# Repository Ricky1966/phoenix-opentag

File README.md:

# Phoenix OpenTag

> [!CAUTION]
> **Experimental hobby project: use it entirely at your own risk.** It comes with no warranty, and the author is **not responsible** for any damage to printers, PCs, hardware, software or data. Read the Disclaimer section of this README before you build, flash or run anything.
>
> *Progetto sperimentale: uso a proprio rischio e pericolo. L'autore non risponde di alcun danno a stampanti, computer, hardware, software o dati.*

A minimal NFC reader and writer for **OpenPrintTag** tags (the Prusa Research standard), based on an **ESP32 + PN5180** and designed to be connected to the Sovol SV08 "Phoenix".

Born as a reduced version of [Odin-ESP32](https://github.com/Ricky1966/Odin-ESP32) (a filament drying station): the hardware initialization comes from Odin's `develop` branch, with a separate parser and checks on NFC reads, but without the web dashboard, heater, environment sensors or multi-spool handling. It validates the reads and integrates with Spoolman and Moonraker.

## ⚠️ Disclaimer: use at your own risk

Phoenix OpenTag is an experimental hobby project, provided **"as is"**, without warranty of any kind. It means flashing firmware, wiring electronics, writing to NFC tags, sending commands to a printer's firmware (Klipper/Moonraker) and installing software on your computers. Mistakes, bugs or incompatibilities can cause failed prints, damage to your printer(s), your computer(s), the ESP32/PN5180 module, the tags or any other hardware or software, loss of data, or other harm.

By building, installing, running or modifying anything here you accept that you do so **entirely at your own risk**. The author and the contributors are **not responsible or liable** for any damage or loss of any kind: printers, PCs, hardware, software, data or anything else. Test carefully, never leave a printer unattended, back up your configuration before changing it, and read the code before you run it. The warranty disclaimer of the AGPL-3.0 licence (sections 15 and 16) applies as well.

*In italiano: progetto sperimentale da usare **a proprio rischio e pericolo**. L'autore non risponde di alcun danno a stampanti, computer, hardware, software o dati.*

---

## What it does

- Connects to the home WiFi (station mode, no Access Point), used for sending in `wifi`/`auto` mode and for OTA updates.
- Continuously reads the ISO15693/NFC-V tags near the PN5180 (the protocol used by OpenPrintTag).
- When it recognizes an OpenPrintTag, it prints on the serial port: brand, material, colour, diameter, density, nozzle/bed temperature range, weight, country.
- Prints the data when the tag changes or a valid read is recovered. It only sends validated data.
- Sends every new read to the daemon on Phoenix, over **USB** or **WiFi** as you choose (see below). The daemon passes it to Spoolman and sets the active spool in Moonraker.
- **Writes** OpenPrintTag images to blank or existing ICODE SLIX2 tags, driven by the Spoolman fork's «Scrivi tag» button, and offers to write a blank tag when one is placed on the reader (see below).

## Writing tags

The firmware writes complete OpenPrintTag images to **ICODE SLIX2 tags with 316 user bytes**, with UID check, protection checks, explicit consent to replace existing data and a full read-back. Serial protocol, command-line client and limits: [procedure and limits](docs/tag-writing.md).

With the [Spoolman fork](https://github.com/Ricky1966/Spoolman) the whole flow runs from the web UI: open a saved spool, press **Scrivi tag**, check the pre-filled data, place the tag and confirm. The tag is linked to the spool only after the firmware has verified it. Validated on real hardware on 1 October 2026. Setup of the authenticated bridge between Spoolman and the daemon is described in [docs/tag-writing.md](docs/tag-writing.md).

A **blank** SLIX2 tag placed on the reader while the printer is idle is reported to Spoolman, which proposes the spool without a tag and asks for confirmation before writing; after a verified write the tag is read again and the spool becomes active. The reader stays disarmed while a print is running or paused, or while Klipper is running G-code (macros, filament loading).

## Hardware

- ESP32 DevKit, 38 pin (AZ-Delivery ESP32-WROOM-32)
- PN5180 module (NXP/AZ-Delivery breakout)
- ICODE SLIX2 tags, jumper wires and a USB data cable

The full **bill of materials**, tag requirements and the **wiring schematic** are in [docs/hardware.md](docs/hardware.md).

Point-to-point wiring:

| PN5180 signal | ESP32 GPIO |
|---|---|
| RST | 17 |
| NSS (CS) | 5 |
| MOSI | 23 |
| MISO | 19 |
| SCK / CLK | 18 |
| BUSY | 16 |
| 5V | 5V |
| 3V3 | 3V3 |
| GND | GND |

## Setup

```bash
cp src/secrets.h.example src/secrets.h
# edit src/secrets.h with the real WiFi SSID/password
pio run --target upload
pio device monitor
```

`src/secrets.h` is not versioned (see `.gitignore`).

## Updating over WiFi (OTA)

Since 0.4.0 the firmware can also be updated over WiFi, without unplugging the ESP32 from Phoenix. WiFi always stays on, even in `usb` mode, because OTA needs it.

1. In `src/secrets.h` add the OTA password (see `secrets.h.example`); without this line OTA stays disabled:
   ```c
   #define OTA_PASSWORD "choose-a-password"
   ```
2. **Once, over USB**, flash the first firmware that has OTA: `pio run -t upload --upload-port <port>`. At start-up you must see `OTA attivo: phoenix-opentag.local (<IP>)`.
3. From then on, from the PC:
   ```bash
   PHOENIX_OTA_PASSWORD='choose-a-password' pio run -e esp32dev_ota -t upload
   ```
   If `phoenix-opentag.local` does not resolve, add `--upload-port <ESP32 IP>` (printed by `show`).

Use only letters and digits for `OTA_PASSWORD`: PlatformIO inserts it into the command without quotes, so `&`, `;`, `$` or spaces break it. `espota.py --debug` prints the password in clear text: do not use it. The password is compiled into the firmware, so changing it requires a new flash over USB.

During the update NFC reading is paused; when it finishes the ESP32 restarts and the daemon on Phoenix resumes reading the serial port by itself.

## Sending to Phoenix: USB or WiFi

The mode is chosen from the serial port (`pio device monitor`, 115200) and is kept in flash, with no recompilation:

| Command | Effect |
|---|---|
| `show` | current settings |
| `mode usb` | every read goes out on the serial port as a `PHOENIX-TAG {json}` line, read by the daemon (default) |
| `mode wifi` | HTTP `POST <host>/tag` with the same JSON |
| `mode auto` | WiFi if connected and the POST succeeds, otherwise USB |
| `host http://<phoenix-ip>:7913` | address of the daemon on Phoenix |
| `reader <id>` | `reader_id` shown in Spoolman (default `phoenix-opentag`) |
| `test` | resend the last tag read |
| `reboot` | restart, required after `mode` |

The initial values are in `src/config.h` (`TRANSPORT_DEFAULT_*`). JSON v1 sent since version 0.5 (fields missing from the tag are omitted; the daemon also accepts the 0.4 names):

```json
{"schema_version":1,"event_id":"12ab34cd-00000001","uid":"E004010812345678","reader_id":"phoenix-opentag","firmware":"0.5.0-dev","brand_name":"Prusament","material_name":"PLA Galaxy Black","color_rgba":"#3D3E3DFF","filament_diameter":1.75,"density":1.24,"nominal_netto_full_weight":1000}
```

The firmware keeps only the latest valid read: it retries after 5, 10, 20, 40 and 60 seconds (maximum), pauses sending on an NFC error and cancels the event when the removal is confirmed. Over USB the daemon replies `ack <event_id>` only after successful handling; over WiFi a Moonraker error produces HTTP 502. The two transports share the same event in `auto` mode. POSTs are synchronous and can temporarily delay NFC polling and OTA. The full contract is in [docs/http-contract.md](docs/http-contract.md).

An activation refused during `printing`/`paused` is a final outcome: it is not queued for the end of the print. After the print you need a new read, or `test`. The weights of spools that are already registered are not updated from the tag.

**Upgrading from 0.4:** install the new daemon first (it is compatible with both formats), then the firmware. Restart only `phoenix-opentag` after updating the files. Verify with a known spool, with the printer idle. Keep `src/secrets.h`, the NVS settings and the `--serial` parameters of the existing service.

## Daemon on Phoenix

`host/phoenix_opentag_daemon.py` runs on the CB1 with the system `python3` (no dependencies). For every read:

1. it calls `POST /api/v1/tag/scan` on Spoolman (≥ 0.27.0), which resolves the UID to the linked spool;
2. if the UID is unknown and the tag carries at least `material` and `density`, it creates the spool, reusing the vendor (`brand`) and filament (name, vendor, colour, diameter) if they already exist, and links the tag to it;
3. it sets the active spool with `POST /server/spoolman/spool_id` on Moonraker, **but not if the printer is `printing` or `paused`**.
4. with `--lane-data` (off by default), it also publishes the active spool to Moonraker's `lane_data` database namespace, see [Loading the filament profile in OrcaSlicer](#loading-the-filament-profile-in-orcaslicer-optional).

Only consecutive identical events handled successfully within 5 s are deduplicated; A → B → A reactivates A. Temporary errors are not remembered as successes. Useful options: `--no-create`, `--no-activate`, `--lane-data`, `-v`.

### Loading the filament profile in OrcaSlicer (optional)

> **Experimental, not yet tested with OrcaSlicer.** Unreleased: the `filament_id` part needs a small OrcaSlicer patch (`orca-patches/0003-moonraker-lane-data-filament-id.patch` in the `sv08-ultimate-build-dev` repository, not merged upstream). Without it, Orca still reads the material, colour and temperatures but picks a generic profile.

With `--lane-data`, after the spool is activated the daemon writes one lane to Moonraker's database (`POST /server/database/item`, namespace `lane_data`, key `lane<N>`, with `N` from `--lane-index`, default `0`):

```json
{"lane": "0", "material": "PLA", "color": "#A1B2C3", "nozzle_temp": 215, "bed_temp": 60, "filament_id": "OFW29a9R"}
```

It is built from the Spoolman filament: `material`, `color_hex`, `settings_extruder_temp`, `settings_bed_temp`, and an optional **text** extra field `orca_filament_id` (create it in Spoolman under Settings → Extra fields → Filament) holding the `filament_id` of the OrcaSlicer profile. The lane is skipped if the filament has no material. A failure here is logged and never undoes the activation. Nothing is written while the printer is `printing` or `paused`, because the activation is skipped then.

The lane also carries two informational fields that OrcaSlicer ignores: `name` (vendor and filament name) and `updated` (UNIX seconds of the read), so a tool can show which tag the lane comes from.

In OrcaSlicer, press *Synchronize filament list* in the sidebar to load the profile: nothing changes by itself. To read what Orca will see: `curl -s "http://localhost:7125/server/database/item?namespace=lane_data"`.

```bash
# manual test on Phoenix
python3 ~/phoenix-opentag/host/phoenix_opentag_daemon.py --listen 0.0.0.0:7913 \
    --serial /dev/serial/by-id/usb-1a86_USB_Serial-if00-port0   # only for usb/auto
curl -s http://localhost:7913/health

# permanent service
sudo cp ~/phoenix-opentag/host/phoenix-opentag.service /etc/systemd/system/
sudo systemctl daemon-reload && sudo systemctl enable --now phoenix-opentag
journalctl -u phoenix-opentag -f
```

To switch the service to USB mode, add `--serial` to the `--listen` line and restart it:

```bash
sudo sed -i 's|--listen 0.0.0.0:7913 \\|--listen 0.0.0.0:7913 --serial /dev/serial/by-id/usb-1a86_USB_Serial-if00-port0 \\|' /etc/systemd/system/phoenix-opentag.service
sudo systemctl daemon-reload && sudo systemctl restart phoenix-opentag
```

To send commands to the ESP32 while it is connected to Phoenix, stop the daemon (`sudo systemctl stop phoenix-opentag`: the port must not be read by two programs) and use the serial monitor included with Klipper. Exit with `Ctrl+]`, which on an Italian keyboard is `Ctrl+5`:

```bash
~/klippy-env/bin/python -m serial.tools.miniterm -e /dev/serial/by-id/usb-1a86_USB_Serial-if00-port0 115200
```

With `--serial` always use the `/dev/serial/by-id/...` path of the ESP32. The daemon refuses to open a port that appears as `serial:` in Klipper's `.cfg` files (`--klipper-config`, default `~/printer_data/config`).

The daemon and Spoolman have no authentication: expose them only on the local network. The writer API of the daemon is disabled unless `PHOENIX_WRITER_TOKEN` is set.

## Validation

PC tests: parser, delivery, ISO15693 driver, 40,000 altered inputs, the six official OpenPrintTag tags, the writer (interruptions at every block, locks, an unwritable block 79) and daemon/bridge regressions (see "PC tests").

**1 October 2026, tag writing: PASS on real hardware.** Writing failed at first because ICODE SLIX2 block 79 is a read-only counter, not user memory; after limiting the writer to the 316 user bytes (blocks 0–78) a tag was restored from a backup (`verified: true`, block 79 untouched), then written from the Spoolman web UI: verified by the firmware, linked to the spool, re-read without creating a duplicate, and the spool made active in Moonraker.

**30 September 2026, consolidated version `0.5.0-dev`: PASS on real hardware.** Flash over USB, then a successful **OTA update over WiFi** with the final password. At start-up: WiFi connected, PN5180 3.5 OK, `OTA attivo`. The ODIN test tag is read and sent as a `PHOENIX-TAG` line (JSON v1). The daemon of this branch, installed on Phoenix in place of the previous version, finds spool 2 again in USB mode (`created: false`) and activates it in Moonraker. Locally, with Spoolman 0.27.0, the daemon creates vendor, filament, spool and link from the firmware line, replies `ack <event_id>`, ignores a repeated `event_id` and does not activate the spool while the printer is `printing`.

Still to verify: that the ESP32 really receives the ACK from the daemon, the `wifi` and `auto` modes with the consolidated firmware, the blank-tag proposal on a real blank tag, and the reading of tags not written by Odin.

Earlier tests, on version 0.4 (0.4 daemon):

**29 September 2026, WiFi mode: PASS on real hardware.** ESP32 DevKit (CH340) + PN5180 3.5, OpenPrintTag test tag (UID `E0:04:01:08:66:07:15:E3`, ODIN Test PLA). Phoenix: Spoolman 0.27.0 in Docker, daemon started by hand with `--listen 0.0.0.0:7913`.

- First read: the daemon created vendor ODIN, filament "Test PLA" and spool 2 with the tag linked, then made it active in Moonraker (`GET /server/spoolman/spool_id` → `2`). Time from read to activation: about 1 s.
- Second read, after removing the tag for more than 5 s: spool 2 found again (`created: false`) and reactivated, no duplicate.

- Daemon installed as a service (`host/phoenix-opentag.service`, `enable --now`): the same read reactivates spool 2; a second tag (UID `E0:04:01:08:66:07:19:17`, BravaSoft Test PLA) creates vendor BravaSoft, a separate filament and spool 3, which becomes the active one.

- **USB mode: PASS.** ESP32 connected to a USB port of Phoenix (`/dev/serial/by-id/usb-1a86_USB_Serial-if00-port0`, next to the Klipper MCU `usb-Klipper_stm32f103xe_...`), service started with `--serial` on that path. The read arrives as `[usb]` and reactivates spool 2.

## PC tests

`bash tests/run_host.sh` (only needs `g++`) builds with AddressSanitizer and tests: the parser and the delivery, the ISO15693 driver and the **six official example tags** of the OpenPrintTag specification (`tests/fixtures/official/`, Prusa Research MIT licence in `tests/fixtures/LICENSE.openprinttag`; expected values generated with their reference Python implementation), the writer and its serial protocol, plus truncations and randomly altered bytes with no out-of-bounds access. The sixth tag has a maximum nozzle temperature below the minimum and is a deliberately invalid case: the parser rejects it. If a tag does not state the diameter, the parser assumes 1.75 mm as the specification says. The Python parts (daemon, writer client, bridge) are tested with `python3 -m unittest discover -s tests -p 'test_*.py'`. GitHub CI runs the same checks and builds the firmware.

The 0.4 parser did not read the official tags (it did not handle the meta section, indefinite-length CBOR maps and long NDEF records): it only worked with tags written by Odin.

## Next steps

- Orca Slicer integration: have the slicer take the active spool from Spoolman/Moonraker (for example with spoolman2slicer or a tap-driven active spool). To be decided.
- Test OpenPrintTag tags from different manufacturers.
- Send the tag's raw memory to Spoolman (`payload_b64` of `POST /tag/scan`, which Spoolman currently retransmits without decoding) and decode it there. The specification and the reference implementation are in the `prusa3d/OpenPrintTag` repository (MIT licence).

## Structure

```
src/
  config.h        PN5180 pins, timing, include of secrets.h
  secrets.h       WiFi credentials (not versioned, see secrets.h.example)
  nfc.h/.cpp      PN5180 reading with error handling, blank-tag detection
  nfc_writer.inc  Serial write protocol (write-info/commit/cancel/resume), included by nfc.cpp
  tag_parser.*    Validated NDEF/CBOR parser, testable without hardware
  tag_writer.*    Verified SLIX2 writer (user blocks 0-78), testable without hardware
  delivery.*      JSON v1 and delivery-attempt state
  transport.h/.cpp  Sending reads to Phoenix (USB/WiFi), serial commands, settings in flash
  main.cpp        setup() + loop(), WiFi and OTA
tests/            PC tests (`bash tests/run_host.sh`, `python3 -m unittest`): parser, delivery, ISO15693, official tags in fixtures/official, writer, daemon, bridge
docs/
  hardware.md       Bill of materials, tag requirements, wiring and assembly checks
  wiring.svg        Wiring schematic
  http-contract.md  Reader -> daemon contract (JSON v1, ACK, retries, blank tag)
  tag-writing.md    Writing tags: protocol, backups, bridge to Spoolman
.github/workflows/check.yml  CI: tests, daemon on Python 3.9, build with and without OTA
host/
  phoenix_opentag_daemon.py  Daemon for Phoenix: serial/HTTP -> Spoolman -> Moonraker
  phoenix_opentag_write.py   Command-line writer client with backups
  phoenix_writer_bridge.py   Authenticated bridge used by the Spoolman fork
  phoenix-opentag.service    systemd unit
lib/PN5180-Library/  Vendored PN5180 library (from Odin-ESP32)
```

## References

- [OpenPrintTag](https://openprinttag.org/) — open-source NFC standard by Prusa Research
- [Odin-ESP32](https://github.com/Ricky1966/Odin-ESP32) — source project (filament dryer)
- [Spoolman fork with the «Scrivi tag» button](https://github.com/Ricky1966/Spoolman)

## Licence

Distributed under the GNU Affero General Public License v3.0.

SPDX-License-Identifier: AGPL-3.0-or-later

The repository includes third-party code and data with their own licences (a modified copy of the PN5180 Library, LGPL-2.1-or-later, and OpenPrintTag test data, MIT): see [NOTICE.md](NOTICE.md).

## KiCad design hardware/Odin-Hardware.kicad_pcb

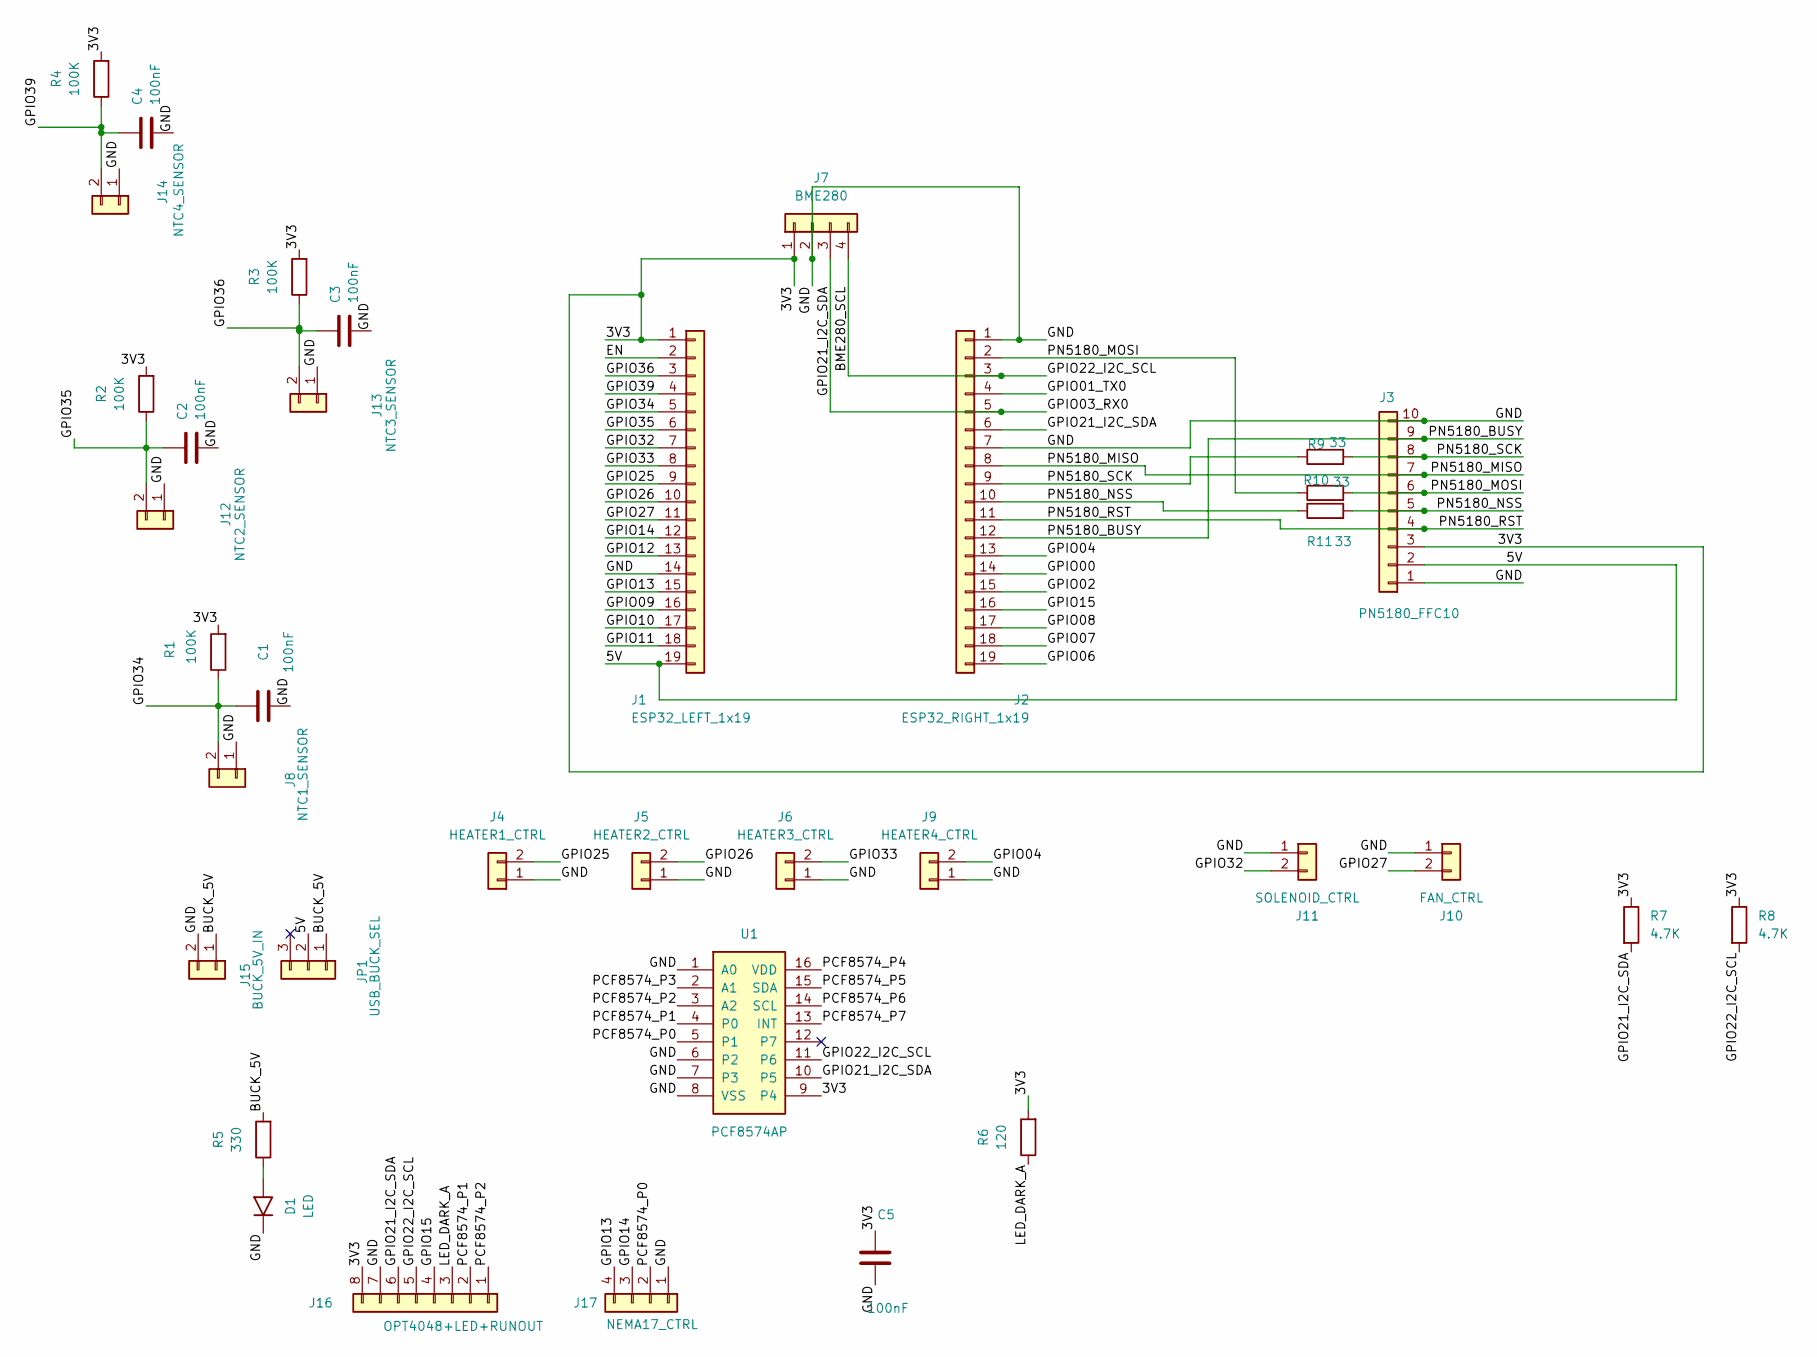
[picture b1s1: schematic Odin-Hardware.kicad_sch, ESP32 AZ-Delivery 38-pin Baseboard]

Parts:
C1, C2, C3, C4, C5: 100nF; C_0805_2012Metric
D1: LED; LED_0805_2012Metric
J1: ESP32_LEFT_1x19; PinSocket_1x19_P2.54mm_Vertical
J2: ESP32_RIGHT_1x19; PinSocket_1x19_P2.54mm_Vertical
J3: PN5180_FFC10; Hirose_FH12-10S-0.5SH_1x10-1MP_P0.50mm_Horizontal
J4: HEATER1_CTRL; JST_XH_B2B-XH-A_1x02_P2.50mm_Vertical
J5: HEATER2_CTRL; JST_XH_B2B-XH-A_1x02_P2.50mm_Vertical
J6: HEATER3_CTRL; JST_XH_B2B-XH-A_1x02_P2.50mm_Vertical
J7: BME280; JST_XH_B4B-XH-A_1x04_P2.50mm_Vertical
J8: NTC1_SENSOR; JST_XH_B2B-XH-A_1x02_P2.50mm_Vertical
J9: HEATER4_CTRL; JST_XH_B2B-XH-A_1x02_P2.50mm_Vertical
J10: FAN_CTRL; JST_XH_B2B-XH-A_1x02_P2.50mm_Vertical
J11: SOLENOID_CTRL; JST_XH_B2B-XH-A_1x02_P2.50mm_Vertical
J12: NTC2_SENSOR; JST_XH_B2B-XH-A_1x02_P2.50mm_Vertical
J13: NTC3_SENSOR; JST_XH_B2B-XH-A_1x02_P2.50mm_Vertical
J14: NTC4_SENSOR; JST_XH_B2B-XH-A_1x02_P2.50mm_Vertical
J15: BUCK_5V_IN; TerminalBlock_Phoenix_MKDS-1,5-2-5.08_1x02_P5.08mm_Horizont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
J16: OPT4048+LED+RUNOUT; Hirose_FH12-8S-0.5SH_1x08-1MP_P0.50mm_Horizontal
J17: NEMA17_CTRL; JST_XH_B4B-XH-A_1x04_P2.50mm_Vertical
JP1: USB_BUCK_SEL; PinHeader_1x03_P2.54mm_Vertical
R1, R2, R3, R4: 100K; R_0805_2012Metric
R5: 330; R_0805_2012Metric
R6: 120; R_0805_2012Metric
R7, R8: 4.7K; R_0805_2012Metric
R9, R10, R11: 33; R_0805_2012Metric
U1: PCF8574AP; DIP-16_W7.62mm

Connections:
/3V3: C5.1, J1.1, J3.3, J7.1, J16.8, R1.2, R2.2, R3.2, R4.2, R6.2, R7.1, R8.1, U1.9 (P4)
/5V: J1.19, J3.2, JP1.2
/BME280_SCL: J2.3, J7.4, J16.5, R8.2, U1.11 (P6)
/BUCK_5V: J15.1, JP1.1, R5.2
/EN: J1.2
/GND: C1.2, C2.2, C3.2, C4.2, C5.2, D1.2 (K), J1.14, J2.1, J2.7, J3.1, J3.10, J4.1, J5.1, J6.1, J7.2, J8.1, J9.1, J10.1, J11.1, J12.1, J13.1, J14.1, J15.2, J16.7, J17.1, U1.1 (A0), U1.6 (P2), U1.7 (P3), U1.8 (VSS)
/GPIO00: J2.14
/GPIO01_TX0: J2.4
/GPIO02: J2.15
/GPIO03_RX0: J2.5, J2.6, J7.3, J16.6, R7.2, U1.10 (P5)
/GPIO04: J2.13, J9.2
/GPIO06: J2.19
/GPIO07: J2.18
/GPIO08: J2.17
/GPIO09: J1.16
/GPIO10: J1.17
/GPIO11: J1.18
/GPIO12: J1.13
/GPIO13: J1.15, J17.4
/GPIO14: J1.12, J17.3
/GPIO15: J2.16, J16.4
/GPIO25: J1.9, J4.2
/GPIO26: J1.10, J5.2
/GPIO27: J1.11, J10.2
/GPIO32: J1.7, J11.2
/GPIO33: J1.8, J6.2
/GPIO34: C1.1, J1.5, J8.2, R1.1
/GPIO35: C2.1, J1.6, J12.2, R2.1
/GPIO36: C3.1, J1.3, J13.2, R3.1
/GPIO39: C4.1, J1.4, J14.2, R4.1
/LED_DARK_A: J16.3, R6.1
/PCF8574_P0: J17.2, U1.5 (P1)
/PCF8574_P1: J16.2, U1.4 (P0)
/PCF8574_P2: J16.1, U1.3 (A2)
/PCF8574_P3: U1.2 (A1)
/PCF8574_P4: U1.16 (VDD)
/PCF8574_P5: U1.15 (SDA)
/PCF8574_P6: U1.14 (SCL)
/PCF8574_P7: U1.13 (INT)
/PN5180_BUSY: J2.12, J3.9
/PN5180_MISO: J2.8, J3.7
/PN5180_MOSI: J2.2, J3.6, R10.1, R10.2
/PN5180_NSS: J2.10, J3.5, R11.1, R11.2
/PN5180_RST: J2.11, J3.4
/PN5180_SCK: J2.9, J3.8, R9.1, R9.2
unnamed: D1.1 (A), R5.1

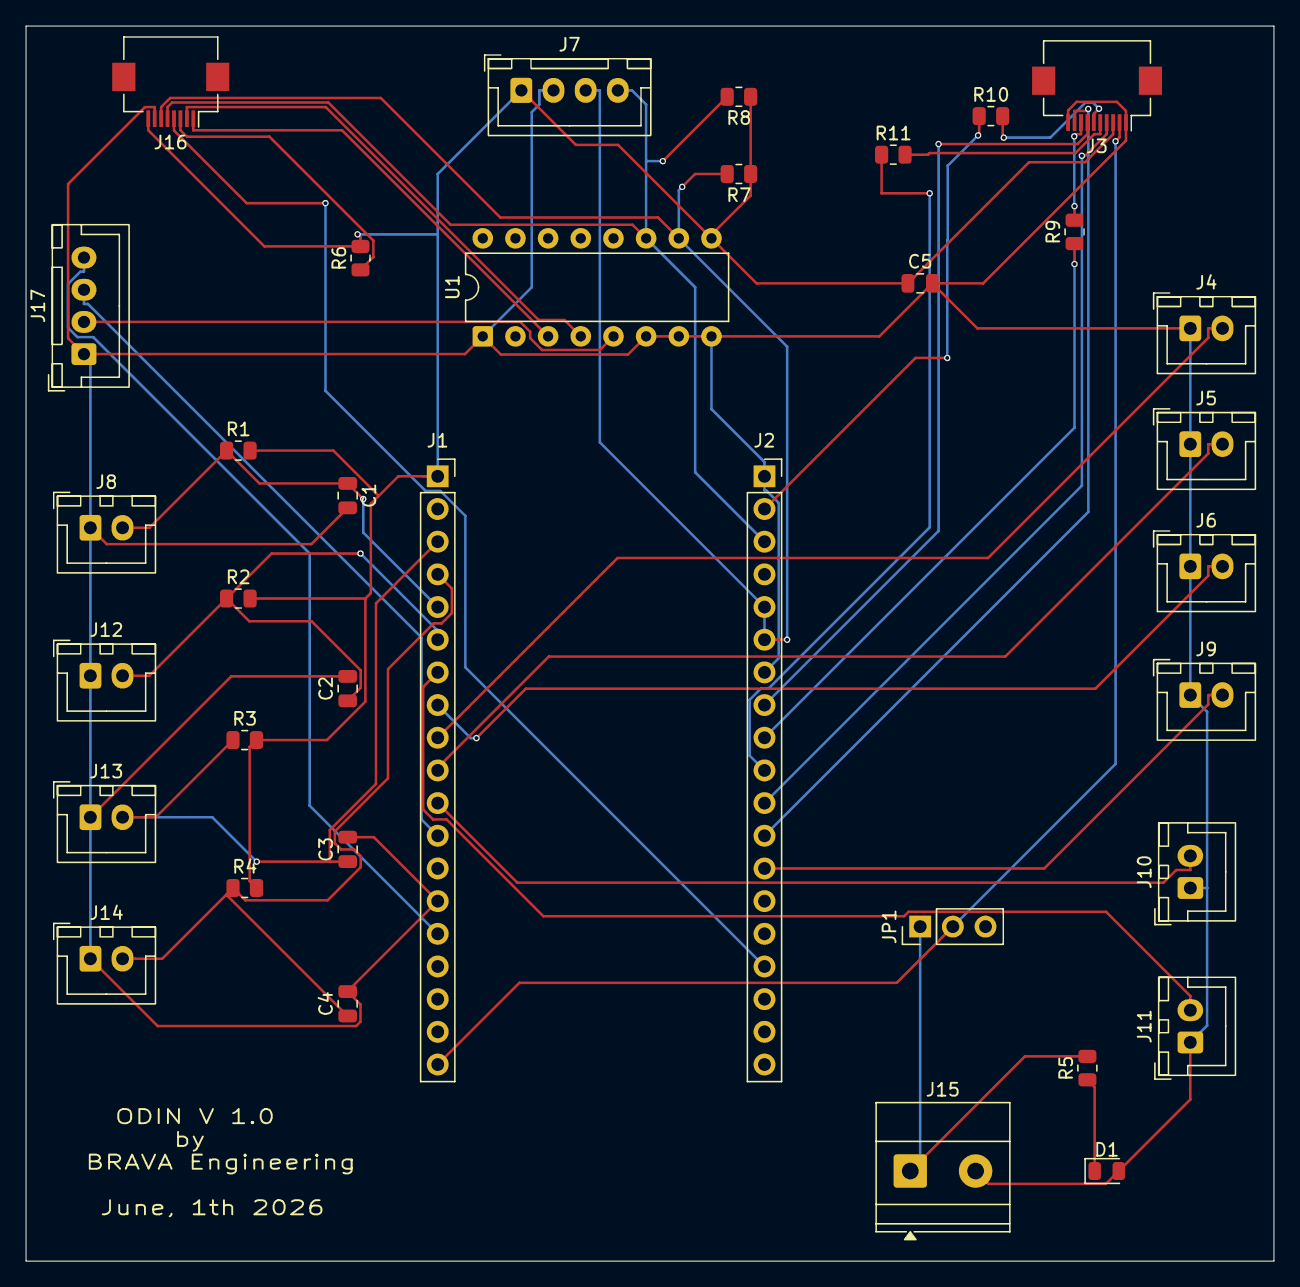
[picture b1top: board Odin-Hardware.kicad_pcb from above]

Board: 2 copper layers, 97.0 x 96.0 mm, 36 parts (0 on the bottom side), 30 nets.

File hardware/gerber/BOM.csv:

Designator,Qty,Value,Description,Package,Manufacturer,MPN,Assembly
"C1,C2,C3,C4,C5",5,100nF,Ceramic Capacitor 100nF X7R 16V ±10%,0805 (2012 Metric),Yageo,CC0805KRX7R9BB104,SMT
D1,1,LED Green,LED Green 2V 20mA,0805 (2012 Metric),Würth Elektronik,150080GS75000,SMT
"R1,R2,R3,R4",4,100KΩ,Resistor 100KΩ 1% 125mW,0805 (2012 Metric),Yageo,RC0805FR-07100KL,SMT
R5,1,330Ω,Resistor 330Ω 1% 125mW,0805 (2012 Metric),Yageo,RC0805FR-07330RL,SMT
R6,1,120Ω,Resistor 120Ω 1% 125mW,0805 (2012 Metric),Yageo,RC0805FR-07120RL,SMT
"R7,R8",2,4.7KΩ,Resistor 4.7KΩ 1% 125mW I2C Pull-up,0805 (2012 Metric),Yageo,RC0805FR-074K7L,SMT
"R9,R10,R11",3,33Ω,Resistor 33Ω 1% 125mW SPI Series Damping,0805 (2012 Metric),Yageo,RC0805FR-0733RL,SMT
J3,1,FH12-10S-0.5SH,FPC/FFC Connector 10-pin 0.5mm pitch Top Contact SMD,SMD,Hirose,FH12-10S-0.5SH(55),SMT
J16,1,FH12-8S-0.5SH,FPC/FFC Connector 8-pin 0.5mm pitch Top Contact SMD,SMD,Hirose,FH12-8S-0.5SH(55),SMT
"J1,J2",2,PinSocket 1x19,Female Pin Header 19-pin 2.54mm pitch Vertical,THT,Generic,—,No Assemble (Customer)
"J4,J5,J6,J8,J9,J10,J11,J12,J13,J14",10,B2B-XH-A,JST XH Connector 2-pin 2.5mm pitch Vertical,THT,JST,B2B-XH-A(LF)(SN),No Assemble (Customer)
"J7,J17",2,B4B-XH-A,JST XH Connector 4-pin 2.5mm pitch Vertical,THT,JST,B4B-XH-A(LF)(SN),No Assemble (Customer)
J15,1,MKDS 1.5/2-5.08,PCB Terminal Block 2-pin 5.08mm pitch Horizontal,THT,Phoenix Contact,1715017,No Assemble (Customer)
JP1,1,PinHeader 1x03,Male Pin Header 3-pin 2.54mm pitch Vertical,THT,Generic,—,No Assemble (Customer)
U1,1,PCF8574AP,8-bit I2C I/O Expander DIP-16,DIP-16,NXP,PCF8574AP,No Assemble (Customer)

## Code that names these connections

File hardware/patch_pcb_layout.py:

#!/usr/bin/env python3
"""
Riposiziona i footprint nella PCB mantenendo J1, J2 fissi
e preservando J7/J8/R1/C1 che hanno già tracce valide.

Layout a blocchi:
  LEFT  (x≈75-93):  NTC circuits  J12/J13/J14 + R2-R4 + C2-C4  +  J15/JP1
  RIGHT (x≈140-155): Heaters J4/J5/J6/J9 + Fans J10/J11 + PN5180 J3
  ABOVE (già ok):   J7 (BME280)  J8/R1/C1 (NTC1)
"""
import re, shutil, sys

PCB = "hardware/ESP32_AZDelivery_Baseboard.kicad_pcb"
shutil.copy(PCB, PCB + ".bak_layout")

with open(PCB) as f:
    txt = f.read()

# ── Nuove posizioni ──────────────────────────────────────────────────────────
# Formato: (x, y, rot)   rot=None → preserva la rotazione attuale
TARGETS = {
    # PN5180 socket: i traces esistenti finiscono a x≈155, y≈100-130
    "J3":  (155.0, 100.0, 0),

    # Heater/Fan JST 2-pin — colonna destra a x=140, spaziatura 10 mm
    "J4":  (140.0, 104.0, 0),   # HEATER1 GPIO25
    "J5":  (140.0, 114.0, 0),   # HEATER2 GPIO26
    "J6":  (140.0, 124.0, 0),   # HEATER3 GPIO33
    "J9":  (140.0, 134.0, 0),   # HEATER4 GPIO4
    "J10": (140.0, 144.0, 0),   # FAN1    GPIO27
    "J11": (140.0, 154.0, 0),   # FAN2    GPIO32

    # NTC2/3/4 JST sensors — colonna sinistra, 3 righe
    "J12": (75.0,  107.0, 0),   # NTC2 GPIO35
    "J13": (75.0,  118.0, 0),   # NTC3 GPIO36
    "J14": (75.0,  129.0, 0),   # NTC4 GPIO39

    # NTC2/3/4 pullup resistors — colonna centrale-sinistra
    "R2":  (85.0,  107.0, 0),
    "R3":  (85.0,  118.0, 0),
    "R4":  (85.0,  129.0, 0),

    # NTC2/3/4 bypass caps — vicino ai resistori
    "C2":  (93.0,  107.0, 90),
    "C3":  (93.0,  118.0, 90),
    "C4":  (93.0,  129.0, 90),

    # Alimentazione BUCK + jumper — sotto le NTC, lato sinistro
    "J15": (80.0,  143.0, 0),
    "JP1": (90.0,  143.0, 0),
}

# ── Funzione di sostituzione ─────────────────────────────────────────────────
def reposition_footprint(content, ref, new_x, new_y, new_rot):
    """
    Trova il blocco footprint con (reference "ref") e aggiorna
    il (at x y [rot]) a livello di footprint (non nelle property figlie).
    Restituisce il contenuto aggiornato + True se trovato.
    """
    # Trova l'inizio del blocco footprint
    # Cerca "(footprint" che contenga (reference "ref")
    # Pattern: da \(footprint fino al blocco instances o fine blocco
    fp_start = re.compile(r'\(footprint\s+"[^"]*"')

    pos = 0
    while True:
        m = fp_start.search(content, pos)
        if not m:
            return content, False

        # Trova la fine di questo blocco (paren matching)
        start = m.start()
        depth = 0
        i = start
        while i < len(content):
            if content[i] == '(':
                depth += 1
            elif content[i] == ')':
                depth -= 1
                if depth == 0:
                    break
            i += 1
        block = content[start:i+1]

        # Controlla se questo blocco contiene la reference giusta
        if f'(property "Reference" "{ref}"' not in block:
            pos = m.end()
            continue

        # Trovato il blocco giusto.
        # Sostituisce il (at x y [rot]) che è figlio DIRETTO del footprint
        # (cioè i primi caratteri dopo la lib_id line, prima delle property)
        # Strategia: trova il primo (at ...) nel blocco che NON sia dentro
        # una sub-espressione profonda (layer, uuid, property...).
        # Più semplice: il (at ...) del footprint è sempre nelle prime righe
        # del blocco, prima di qualsiasi (property ...

        # Trova la posizione del primo "(at " nel blocco
        # che sia sulla stessa "profondità 1" del blocco footprint
        at_pat = re.compile(r'\(at\s+([\d\.\-]+)\s+([\d\.\-]+)(?:\s+([\d\.\-]+))?\)')

        # Scansiona il blocco a profondità 1
        block_inner_start = m.end() - start  # dopo "(footprint "..."
        d = 1
        j = block_inner_start
        at_match = None
        while j < len(block):
            c = block[j]
            if c == '(':
                d += 1
                if d == 2:
                    # Inizio di un figlio diretto
                    m2 = at_pat.match(block, j)
                    if m2:
                        at_match = m2
                        break
            elif c == ')':
                d -= 1
            j += 1

        if not at_match:
            print(f"  WARN: (at) non trovato nel blocco {ref}", file=sys.stderr)
            return content, False

        # Costruisce il nuovo (at ...)
        old_rot = at_match.group(3)
        if new_rot is not None:
            new_rot_str = f" {new_rot}" if new_rot != 0 else ""
        else:
            new_rot_str = f" {old_rot}" if old_rot else ""

        new_at = f"(at {new_x} {new_y}{new_rot_str})"

        # Posizioni assolute nel file originale
        abs_at_start = start + at_match.start()
        abs_at_end   = start + at_match.end()

        content = content[:abs_at_start] + new_at + content[abs_at_end:]
        return content, True

# ── Applica tutte le sostituzioni ────────────────────────────────────────────
for ref, (x, y, rot) in TARGETS.items():
    txt, ok = reposition_footprint(txt, ref, x, y, rot)
    if ok:
        print(f"  ✓ {ref:6s} → ({x}, {y}) rot={rot}")
    else:
        print(f"  ✗ {ref:6s} NON TROVATO", file=sys.stderr)

# ── Salva ────────────────────────────────────────────────────────────────────
with open(PCB, 'w') as f:
    f.write(txt)

print("\n✓ Layout PCB aggiornato.")
print("  Apri in KiCad e verifica DRC/ratsnest; poi effettua il routing.")

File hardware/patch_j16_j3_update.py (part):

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         6=LED_DARK_A, 7=PCF8574_P1, 8=PCF8574_P2
  - Rimuove D2 (LED va nella scatolina FreeCAD)
  - Mantiene R6 (resistenza di limitazione rimane su PCB)
  - Aggiunge label LED_DARK_A su R6 Pin2

J3 (PN5180 FFC 10-pin):
  - Cambia cy da 73.66 a 71.12 (pin 1 rimane a y=68.58)
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        print('WARNING: D2 non trovato')

    # ------------------------------------------------------------------ #
    # F. Remove D2 cathode label PCF8574_P1 at (158.75, 182.88, 270)
    # ------------------------------------------------------------------ #
    removed = False
    start, end = find_block(content, 'label',
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    if start is not None:
        content = remove_block(content, start, end)
        removed = True
    print(f'Label PCF8574_P1@D2 {"rimosso" if removed else "non trovato"}')

    # ------------------------------------------------------------------ #
    # G. Remove wire R6 Pin2 → D2 Anode: (158.75,173.48)→(158.75,175.26)
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        ('LED_DARK_A',     90.17, 187.96, 90),
        ('PCF8574_P1',     92.71, 187.96, 90),
        ('PCF8574_P2',     95.25, 187.96, 90),
        # J17 (unchanged: GPIO13,GPIO14,PCF8574_P0,GND)
        ('GPIO13',        100.33, 187.96, 90),
        ('GPIO14',        102.87, 187.96, 90),
        ('PCF8574_P0',    105.41, 187.96, 90),
        ('GND',           107.95, 187.96, 90),
    ]
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    print(f'Aggiunti {len(new_labels)} label a y=187.96 (J16×8 + J17×4)')

    # ------------------------------------------------------------------ #
    # I. Add LED_DARK_A label on R6 Pin2 (158.75, 173.48, rot=270)
    # ------------------------------------------------------------------ #
    idx = content.find(marker)
    content = content[:idx] + label('LED_DARK_A', 158.75, 173.48, 270) + content[idx:]
    print('Aggiunto label LED_DARK_A su R6 Pin2')

    # ------------------------------------------------------------------ #
    # J. Add J3 pin10: wire (214.63,91.44)→(228.60,91.44) + GND label
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
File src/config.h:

#pragma once
#include <Arduino.h>

// Firmware version
#define PHOENIX_FW_VERSION "0.6.0-dev"

// PN5180 SPI — bus condiviso (SCK18/MISO19/MOSI23), CS/BUSY/RST dedicati
constexpr uint8_t PN5180_NSS  = 5;   // chip-select
constexpr uint8_t PN5180_BUSY = 16;  // input
constexpr uint8_t PN5180_RST  = 17;  // reset

constexpr unsigned long NFC_POLL_MS = 1500;  // cadenza polling lettore NFC

// Invio letture al demone su Phoenix: valori iniziali, modificabili da seriale
// (comandi mode/host/reader, vedi transport.h) e poi conservati in flash.
#define TRANSPORT_DEFAULT_MODE   "usb"                        // usb | wifi | auto
#define TRANSPORT_DEFAULT_HOST   "http://phoenix.local:7913"    // demone su Phoenix: imposta il tuo con il comando seriale host
#define TRANSPORT_DEFAULT_READER "phoenix-opentag"

// Nome di rete per l'OTA: phoenix-opentag.local (password OTA_PASSWORD in secrets.h)
#define OTA_HOSTNAME "phoenix-opentag"

// WiFi (stazione, nessun Access Point). Credenziali vere in secrets.h (non versionato).
#include "secrets.h"

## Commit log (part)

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2026-05-10 Aggiungi README iniziale
2026-05-10 modifica readme
2026-05-10 aggiunta la licenza
2026-05-10 Prima prova per compilazione ESP32
2026-05-10 aggiunta pagina web con temperatura pressione e umidità
2026-05-10 aggiunto pn5180
2026-05-10 sistemato portale e pn5180 per lettura ISO 14443A
2026-05-10 modifiche di stabilità per PN5180
2026-05-10 Vendor PN5180 library locally
2026-05-13 modificato e aggiunto mosfet e ntc per piatto cone stabilità libreria
2026-05-14 modifiche al PI
2026-05-14 cominciamo lettura tag OpenPrintTag
2026-05-16 Modifiche varie al main
2026-05-16 modificato KI a 0.010
2026-05-16 errore corretto in platformio.ini
2026-05-17 Modifiche alle K
2026-05-18 Creazione ramo di localizzazione
2026-05-19 Modifiche alla documentazione e alle traduzioni
2026-05-22 Piccolo aggiustamento sull'api di comunicazione e aggiunta progetti Kicad
2026-05-22 Modifiche allo schematic di kicad
2026-05-23 modifiche a Kicad
2026-05-23 modifica a kicad schematic
2026-05-23 modifiche a Kicad files
2026-05-26 gitignore: escludi file FreeRouting (*.dsn, *.ses)
2026-05-26 PCB: aggiunge BOM.csv per PCBWay PCBA
2026-05-28 piccola modifica
2026-05-30 incolonnato tabella
2026-05-31 Aggiorna TODO: profili su Pi5 completato
2026-06-02 Aggiorna TODO: pagina TAG completata
2026-06-02 Aggiorna TODO sessione odierna
2026-06-02 VS Code: sposta HTTPClient e WiFiClientSecure in cima agli include
2026-06-03 Aggiorna TODO: SetPoint UX completato
2026-06-03 Settings: riduci delay reload a 500ms
2026-06-03 TODO: profili dopo reboot già risolti da migrazione Pi5
2026-06-03 Aggiorna TODO: testi misti e IP navbar completati
2026-06-03 TODO: riavvio guidato e OTA completati
2026-06-11 Fix: aggiungi include translations.h in web_ui.cpp
2026-06-11 Versione 0.9.1: i18n da Cloud, fix porta ESP32 nel backend, app Flutter completa
